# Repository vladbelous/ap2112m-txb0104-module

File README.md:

# AP2112M 3.3V-regulator with TXB0104 logic level shifter

Simple module for AP2112M 3.3V regulator (5V -> 3.3V), combined with TXB0104-based logic level shifter.

AP2112M is 8-SOIC (3.90mm width) and TXB0104 is 14-SOIC (3.90mm width).

Minimal components include 4 capacitors (2 x 1uF in 1206, and 2 x 0.1uF in 805), and one pull-down resistor (in 805).

Optional:
* ON/OFF SPDT switch (if not placed, solder a wire between EN and 5V, i.e. between pins under "ON" text)
* Micro USB (type B) connector. Use 4-leg footprint (available on various different sites)
* If Micro USB is used, place either D1 (for extra safety), or solder JP1 jumper (e.g. 0R in 805)
* JST PH (2.0mm) side conentor - may be useful for powering boards with such battery connector.

A version of this PCB (with round holes for micro USB) can be [ordered on PCBs.io](https://PCBs.io/share/rb7jV).

Designed with [KiCad 5](www.kicad-pcb.org).

## Schematic:

## Layout:

## Render (PCBs.io):

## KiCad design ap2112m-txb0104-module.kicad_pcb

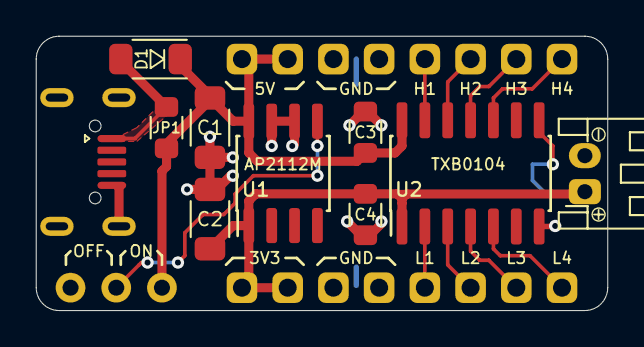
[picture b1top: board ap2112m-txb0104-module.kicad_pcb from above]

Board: 2 copper layers, 31.8 x 15.2 mm, 22 parts (1 on the bottom side), 13 nets.

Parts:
C1, C2: 1u; 1206_HS
C3, C4: 0.1u; 0805_HS
D1: D_Schottky; 1206_Diode_HS
J1: USB_B_Micro; USB-micro-B_4-legs_Banggood
J2, J3: VIN_HV; Pin_Header_Straight_1x01_Pitch2.54mm
J4, J5, J8, J9: GND; Pin_Header_Straight_1x01_Pitch2.54mm
J6, J7: VOUT_LV; Pin_Header_Straight_1x01_Pitch2.54mm
J10: SIG_HV; Pin_Header_Straight_1x04_Pitch2.54mm
J11: SIG_LV; Pin_Header_Straight_1x04_Pitch2.54mm
JP1: 0 Ohm; 0805_HS
JST_PH_BAT1: JST_PH_BAT; JST_PH_S2B-PH-K_02x2.00mm_Angled_WiderHole
R1: 10k; 0805_HS
SW1: SW_REG; Conn_01x03_small
U1: AP2112M-8SOIC; SOIC-8_3.9x4.9mm_Pitch1.27mm_HS
U2: TXB0104; SOIC-14_3.9x8.7mm_Pitch1.27mm_HS

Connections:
3V3: C2.1, C4.1, J6.1, J7.1, JST_PH_BAT1.1, R1.1, U1.1, U2.1, U2.8
5V: C1.1, C3.1, D1.1, J2.1, J3.1, JP1.2, SW1.3, U1.8, U2.14
EN: SW1.2, U1.5
GND: C1.2, C2.2, C3.2, C4.2, J1.5, J1.6, J4.1, J5.1, J8.1, J9.1, JST_PH_BAT1.2, R1.2, SW1.1, U1.6, U1.7, U2.7
H1: J10.1, U2.13
H2: J10.2, U2.12
H3: J10.3, U2.11
H4: J10.4, U2.10
L1: J11.1, U2.2
L2: J11.2, U2.3
L3: J11.3, U2.4
L4: J11.4, U2.5
unnamed: D1.2, J1.1, JP1.1

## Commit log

2019-04-11 Complete schematic
2019-04-12 Create/assign footprints, export netlist
2019-04-12 Component placement, outline, no routing
2019-04-13 Finish routing and silkscreen
2019-04-13 Add images and README
2019-04-13 Update README, add renders, add gerbers for round-hole variant

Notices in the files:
ap2112m-txb0104-module.kicad_pcb:
CC BY-SA 4.0
